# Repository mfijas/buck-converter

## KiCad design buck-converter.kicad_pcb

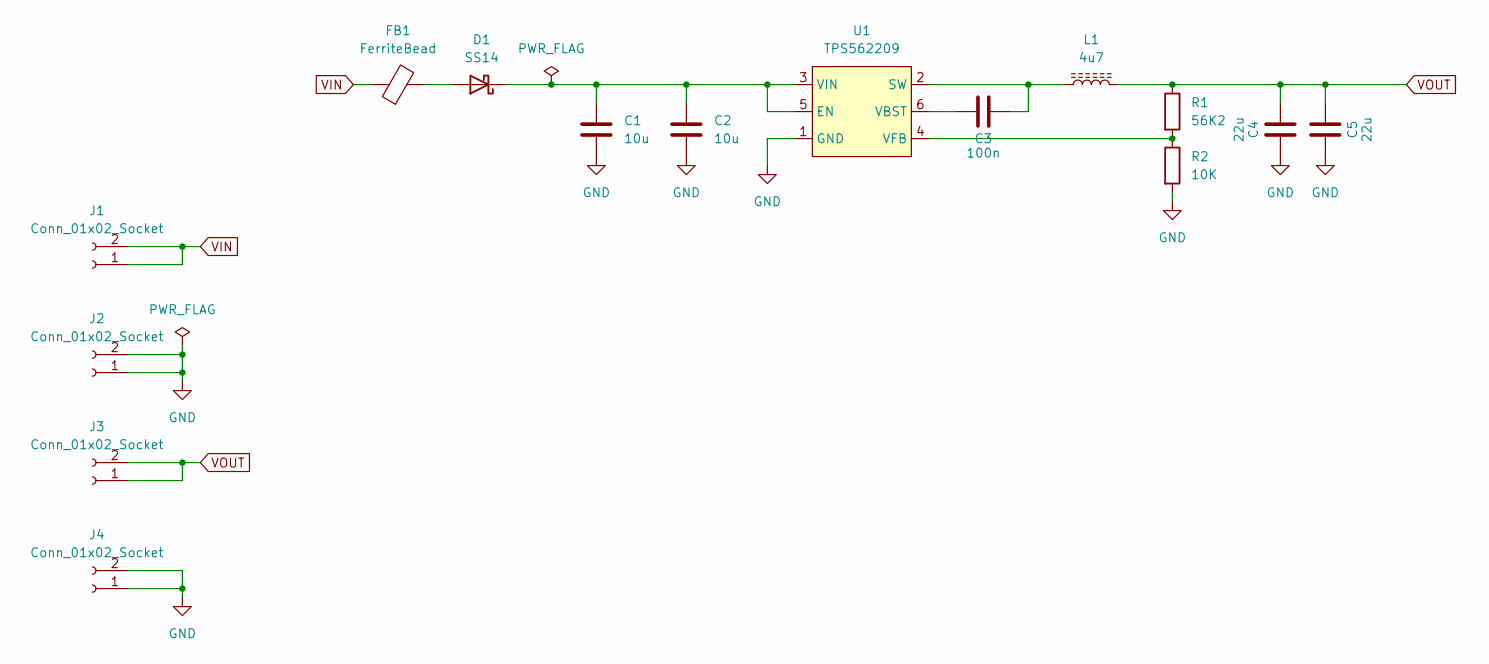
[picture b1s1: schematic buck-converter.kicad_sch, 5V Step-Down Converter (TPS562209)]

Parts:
C1, C2: 10u; C_0805_2012Metric_Pad1.18x1.45mm_HandSolder
C3: 100n; C_0805_2012Metric_Pad1.18x1.45mm_HandSolder
C4, C5: 22u; C_0805_2012Metric_Pad1.18x1.45mm_HandSolder
D1: SS14; D_SMA
FB1: FerriteBead; L_0805_2012Metric_Pad1.05x1.20mm_HandSolder
J1, J2, J3, J4: Conn_01x02_Socket; PinHeader_1x02_P2.54mm_Vertical
L1: 4u7; L_Bourns_SRN6045TA
R1: 56K2; R_0805_2012Metric_Pad1.20x1.40mm_HandSolder
R2: 10K; R_0805_2012Metric_Pad1.20x1.40mm_HandSolder
U1: TPS562209; SOT-23-6_Handsoldering

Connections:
/VINF: C1.1, C2.1, D1.1 (K), U1.3 (VIN), U1.5 (EN)
GND: C1.2, C2.2, C4.1, C5.2, J2.1, J2.2, J4.1, J4.2, R2.2, U1.1 (GND)
unnamed: D1.2 (A), FB1.2
unnamed: C3.1, L1.1, U1.2 (SW)
unnamed: C3.2, U1.6 (VBST)
unnamed: R1.2, R2.1, U1.4 (VFB)
VIN: FB1.1, J1.1, J1.2
VOUT: C4.2, C5.1, J3.1, J3.2, L1.2, R1.1

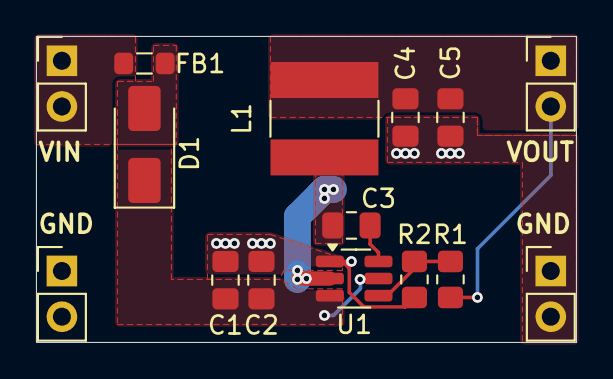
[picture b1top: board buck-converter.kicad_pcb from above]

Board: 2 copper layers, 30.0 x 17.0 mm, 15 parts (0 on the bottom side), 8 nets.

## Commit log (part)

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2025-03-07 Added *.kicad_prl-bak to .gitignore
2025-03-07 ERC fixes
2025-03-07 Version 1.0
2025-03-08 Added output jobset
2025-03-08 Added archive generation to jobset
2025-03-08 Created github action to generate manufacturing output files
2025-03-08 experiments with github actions
2025-03-08 Update GitHub Action to upload Gerber files instead of output
2025-03-08 Update GitHub Action to upload JLCPCB zip file instead of KiCad outputs
